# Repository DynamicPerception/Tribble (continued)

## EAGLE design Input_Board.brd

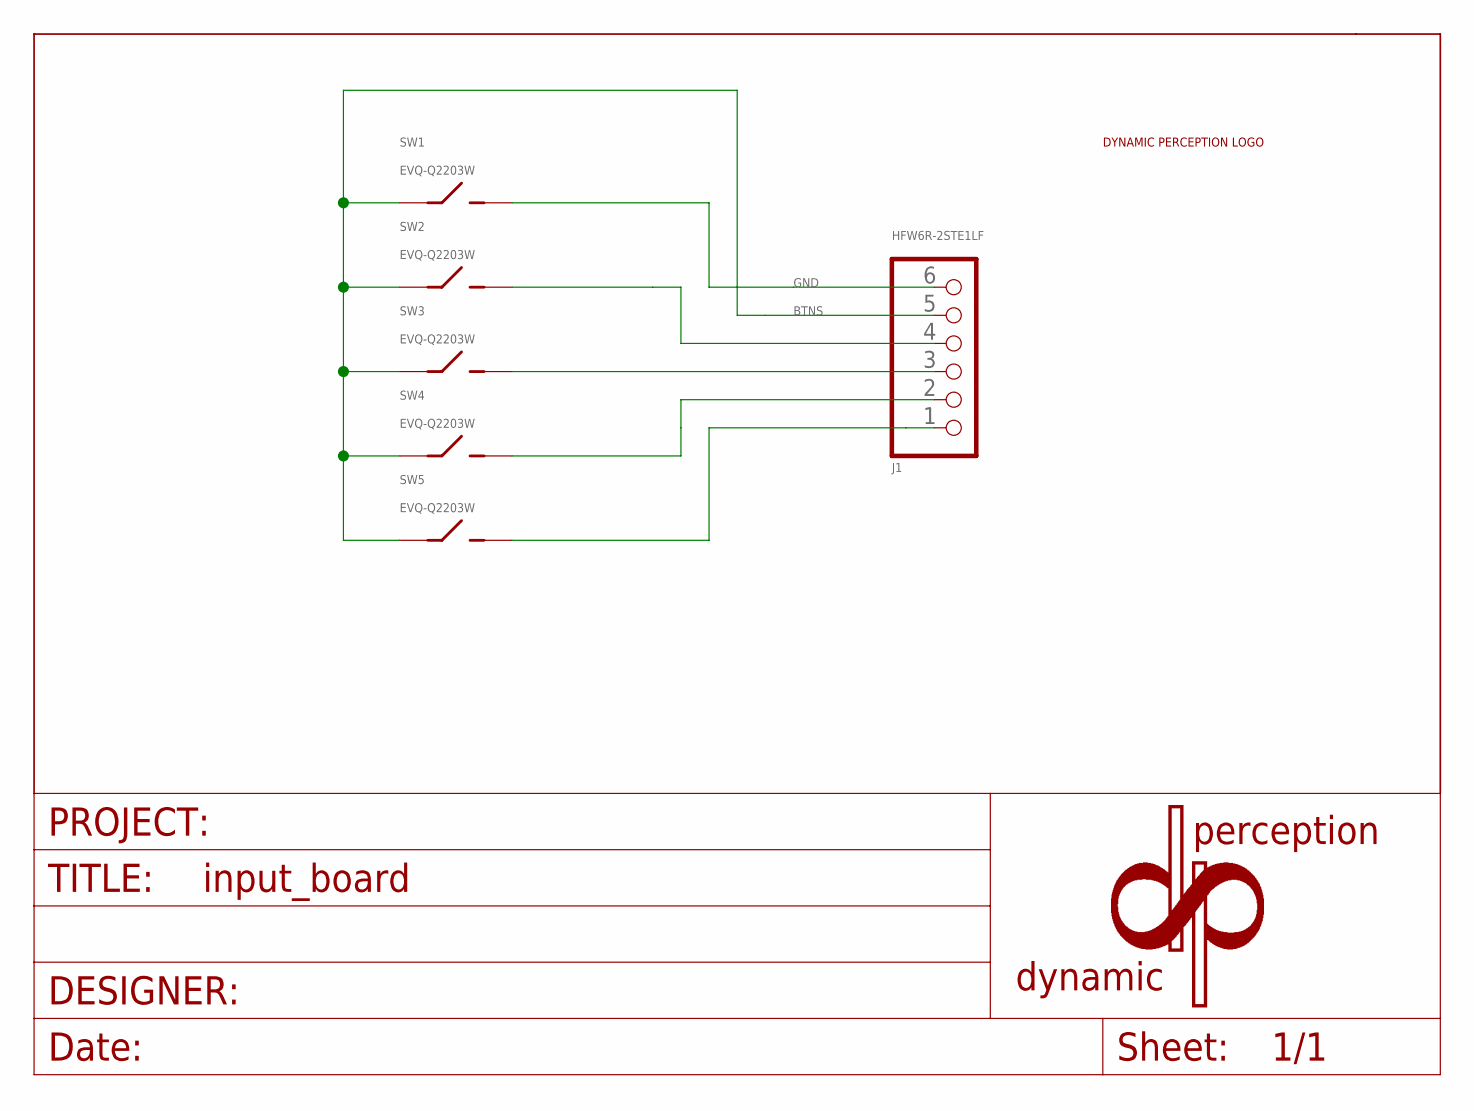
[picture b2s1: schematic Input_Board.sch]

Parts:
FRAME1: DYNAMIC_PERCEPTION_FRAMEPCB_INFO; DYNAMIC_PERCEPTION_FRAME
J1: HFW6R-2STE1LF
LOGO2: DYNAMIC_PERCEPTION_LOGOMICRO; DP_LOGO_MICRO
SW1, SW2, SW3, SW4, SW5: EVQ-Q2203W

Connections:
BTNS: J1.5, SW1.1 (A), SW1.2 (A), SW2.1 (A), SW2.2 (A), SW3.1 (A), SW3.2 (A), SW4.1 (A), SW4.2 (A), SW5.1 (A), SW5.2 (A)
GND: J1.6, SW1.3 (B), SW1.4 (B)
unnamed: J1.4, SW2.3 (B), SW2.4 (B)
unnamed: J1.3, SW3.3 (B), SW3.4 (B)
unnamed: J1.2, SW4.3 (B), SW4.4 (B)
unnamed: J1.1, SW5.3 (B), SW5.4 (B)

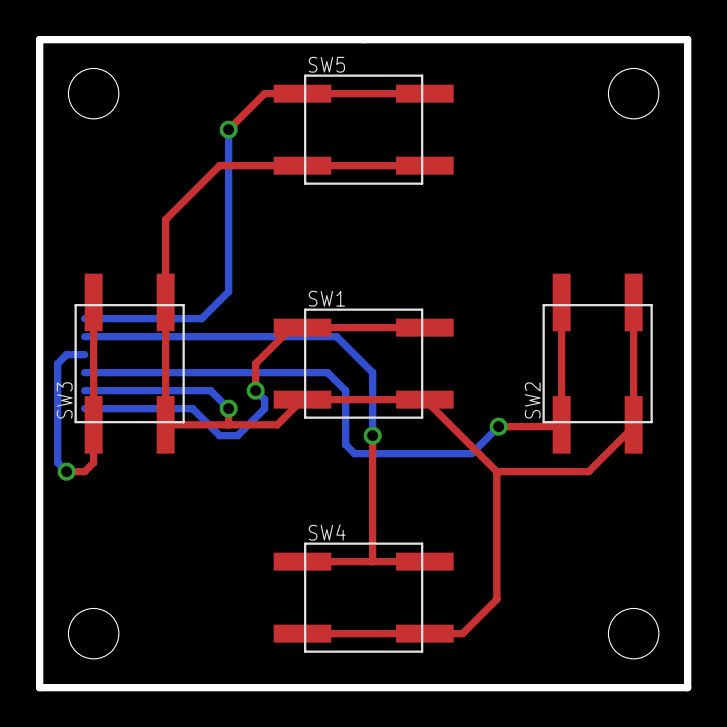
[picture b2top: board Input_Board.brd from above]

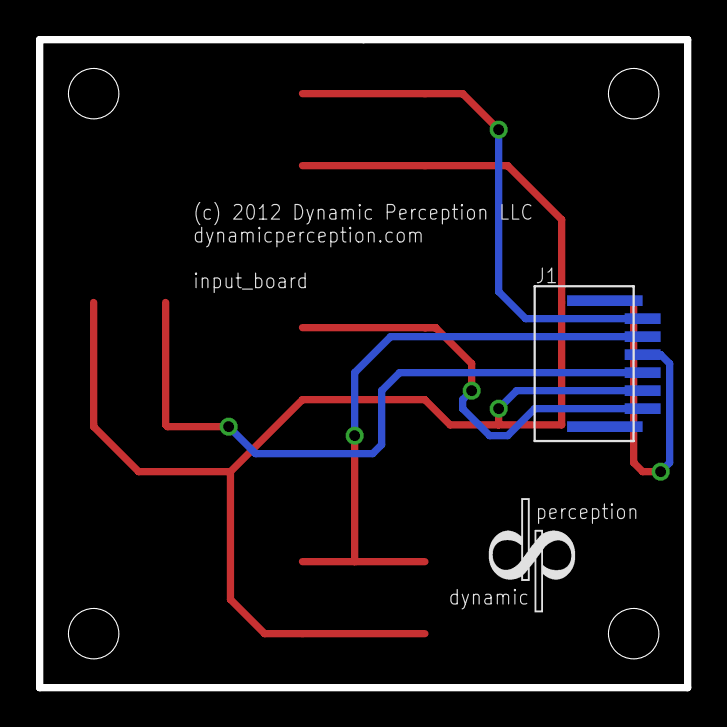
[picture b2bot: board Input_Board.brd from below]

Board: 2 copper layers, 36.0 x 36.0 mm, 8 parts (3 on the bottom side), 6 nets.

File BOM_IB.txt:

Partlist

Exported from Input_Board.sch at 3/18/2013 1:31:10 PM

EAGLE Version 6.2.0 Copyright (c) 1988-2012 CadSoft

Assembly variant: 

Part     Value          Device         Package       Library              Sheet

J1       HFW6R-2STE1LF  PH_1X06FFC     HFW6R-2STE1LF PP_Connectors        1
SW1      EVQ-Q2203W     SPSTEVQ-Q2203W EVQ-Q2203W    PP_Electromechanical 1
SW2      EVQ-Q2203W     SPSTEVQ-Q2203W EVQ-Q2203W    PP_Electromechanical 1
SW3      EVQ-Q2203W     SPSTEVQ-Q2203W EVQ-Q2203W    PP_Electromechanical 1
SW4      EVQ-Q2203W     SPSTEVQ-Q2203W EVQ-Q2203W    PP_Electromechanical 1
SW5      EVQ-Q2203W     SPSTEVQ-Q2203W EVQ-Q2203W    PP_Electromechanical 1

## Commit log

2012-11-21 readding trunk
2012-11-21 checking in changed to the SDB and adding 2 libraries
2012-11-26 finished routing. needs optimizing for SDB
2012-11-28 added jumper to bridge VUSB and +5V so the usb can power the device for testing
2012-11-29 finished SDB REV2
2012-12-03 finished REV2 of SDB
2012-12-03 yup!
2012-12-04 added digital pin numbers to the SDB pin mapping
2013-01-03 REV 3 of SDB in works. Fixed the pull up on the BTNS, changes RS485 chip to one with ESD built in.
2013-01-11 REV 7 of the USB Board done. Moving to production on it.
    SDB Rev 3 almost done. OTG USB added. Motor controllers switched to BTM7755 to reduce the Resistance on of the drivers.
2013-01-15 added 0805 package to pp_passives for resistors. changed resistors on the motor output lines from 0402 to 0805 for better heat dissipation.
2013-01-15 updated cam files for trunk (REV3) of the Super Dolly Board
2013-01-18 Tagged SDB REV_3
2013-02-04 working on SDB REV4
2013-02-05 working on REv 4 of SDB
2013-02-06 added a new PP_Sensor library and more parts to the datasheets
2013-02-07 REV4 of SDB complete. added 2 parts to datasheets and libraires.
2013-02-08 added a part to PP_poweric and replaced the switcher regulator with a linear one.
2013-02-12 changed ESD protection to TPD1E10B06DPYR
2013-02-18 added input board
2013-02-22 fixed a part number issue
2013-03-18 Fixed some small isues with the SDM REV4 and tagged it as REV5. Added the spreadsheet BOM.
2013-03-20 Sketchup and DXF of the SDB
2013-04-01 added FAB checklists for USB->RS485 and SDB
2013-04-24 Changed name of SDB to Tribel. Camfiles for Reg Volt Booster added.
2013-04-24 Changed the name of "tribel" to "tribble" cause I don't watch star trek.
2013-04-24 Adding new cam files for Tribble
2013-04-24 removing old files
2013-04-25 Finished RVB REV0
2013-04-26 fixed minor issues with REV6.
2013-05-10 Fixing EMC problems with Tribble. Moved lots of traces. Added Ferrite beads to COM1, COM2, Com3. Added proper support for USB OTG
2013-05-13 tagged REV_7 of Tribble
2013-05-22 updated the BOM info for Tribble Rev 7
2013-06-07 Fixed the issues for Tribble that popped up during EMC testing
2013-07-03 tagged loads of PCBs and made sure BOMs where up to date
2013-07-11 * Added README
2013-08-08 Revert to REV 7 of Tribble
    Did not need the board fixes in REV 8 of the pcb.
